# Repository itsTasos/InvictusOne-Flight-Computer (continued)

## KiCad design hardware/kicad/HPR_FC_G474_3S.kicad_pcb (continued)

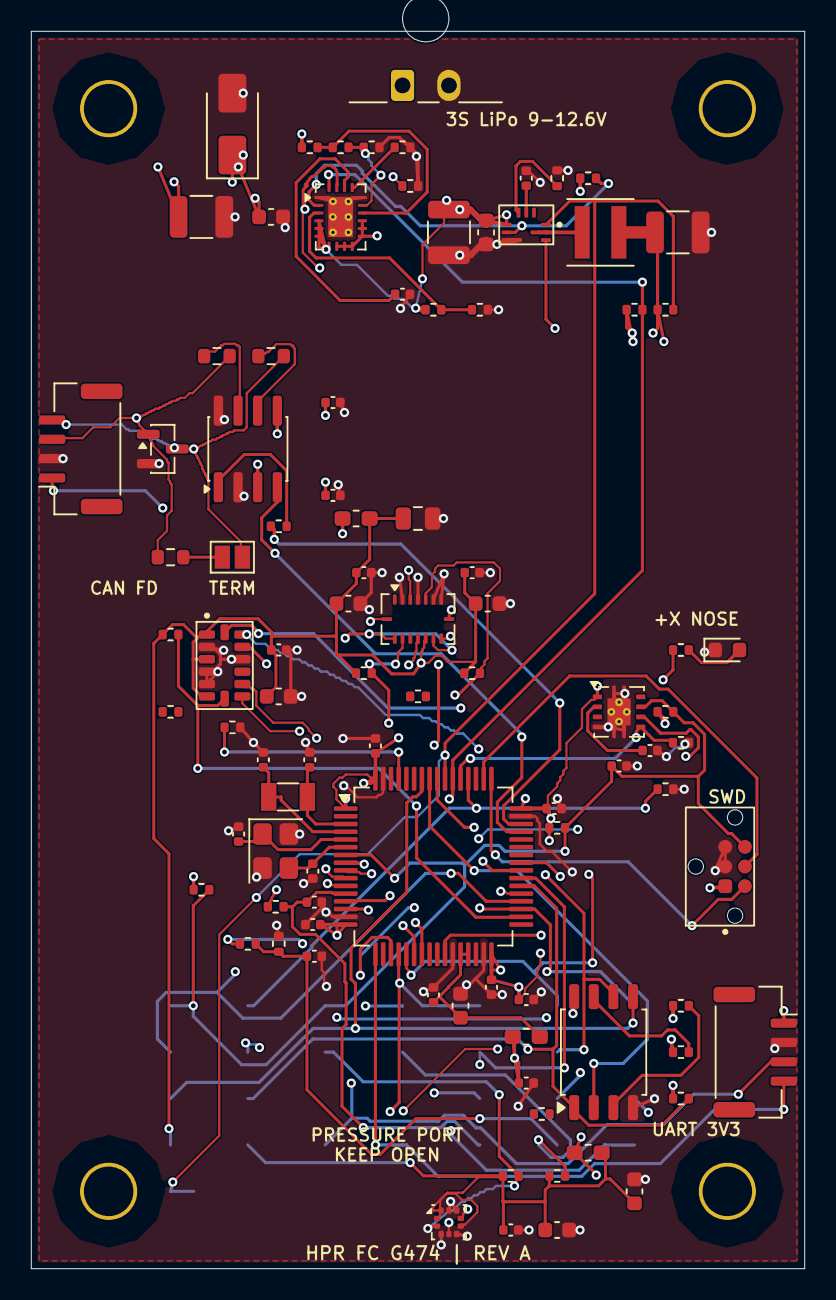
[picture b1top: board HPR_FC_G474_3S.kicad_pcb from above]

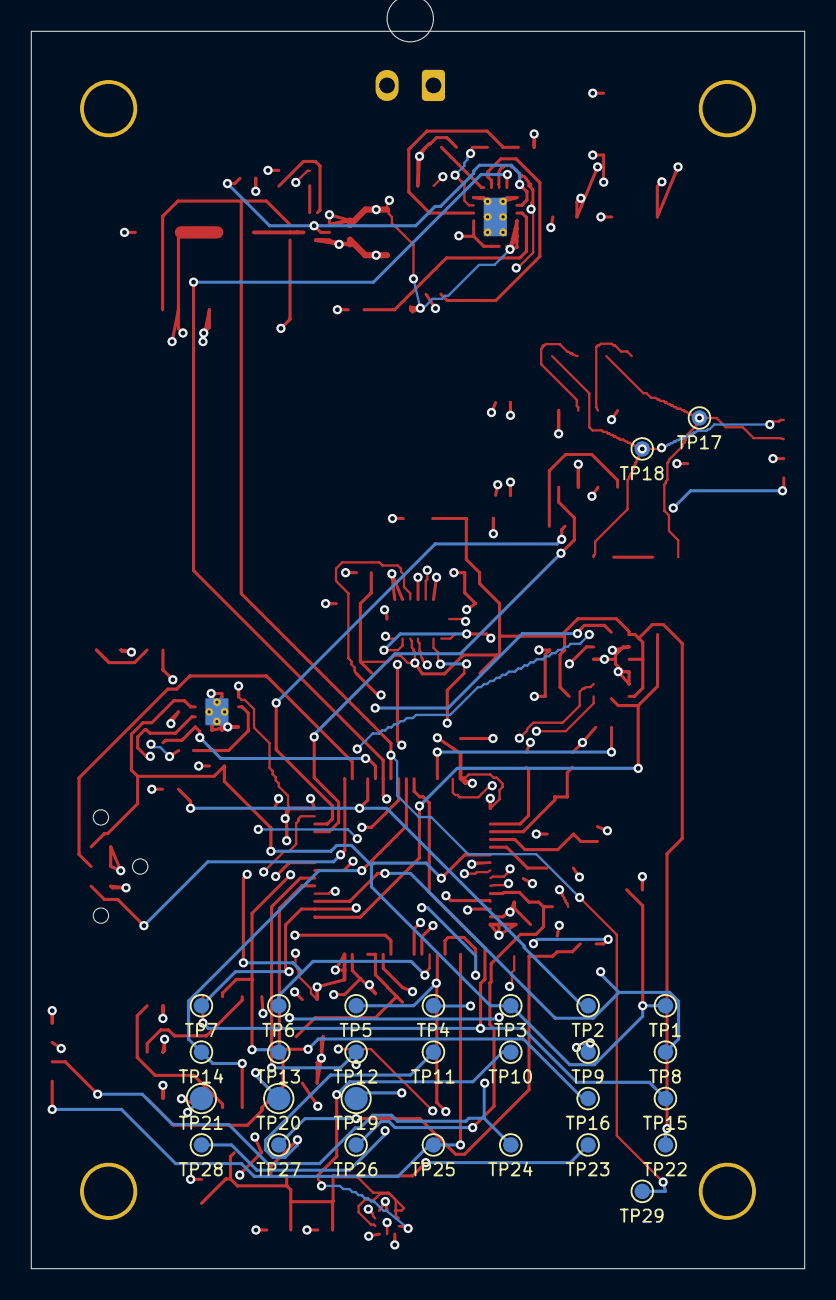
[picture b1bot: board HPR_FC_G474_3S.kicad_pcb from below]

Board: 4 copper layers, 50.0 x 80.0 mm, 127 parts (29 on the bottom side), 66 nets.

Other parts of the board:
H1: MountingHole; HPR_H1_verified_geometry
H2: MountingHole; HPR_H2_verified_geometry
H3: MountingHole; HPR_H3_verified_geometry
H4: MountingHole; HPR_H4_verified_geometry
